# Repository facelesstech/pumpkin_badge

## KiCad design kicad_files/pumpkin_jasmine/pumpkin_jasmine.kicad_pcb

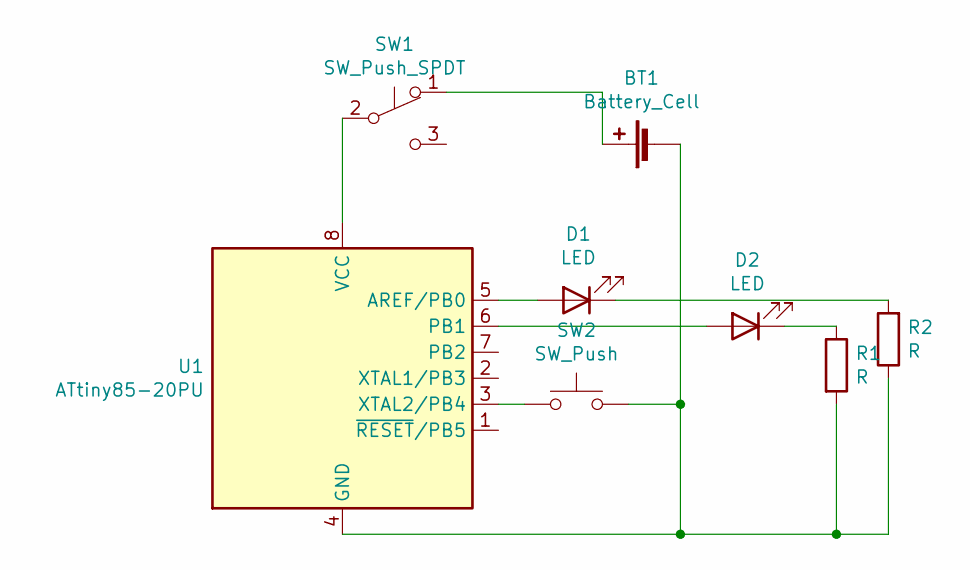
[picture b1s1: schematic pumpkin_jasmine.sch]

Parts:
BT1: Battery_Cell; Keystone_3034_1x20mm-CoinCell
D1, D2: LED; LED_D3.0mm
R1, R2: R; R_Axial_DIN0414_L11.9mm_D4.5mm_P7.62mm_Vertical
SW1: SW_Push_SPDT; 3_pin_switch_smd_side_mount
SW2: SW_Push; SMD_2pin_button_custom
U1: ATtiny85-20PU; DIP-8_W7.62mm

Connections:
unnamed: BT1.1 (+), SW1.1 (A)
unnamed: BT1.2 (-), R1.2, R2.1, SW2.2, U1.4 (GND)
unnamed: D1.1 (K), R2.2
unnamed: D1.2 (A), U1.5 (AREF/PB0)
unnamed: D2.1 (K), R1.1
unnamed: D2.2 (A), U1.6 (PB1)
unnamed: SW1.2 (B), U1.8 (VCC)
unnamed: SW2.1, U1.3 (XTAL2/PB4)

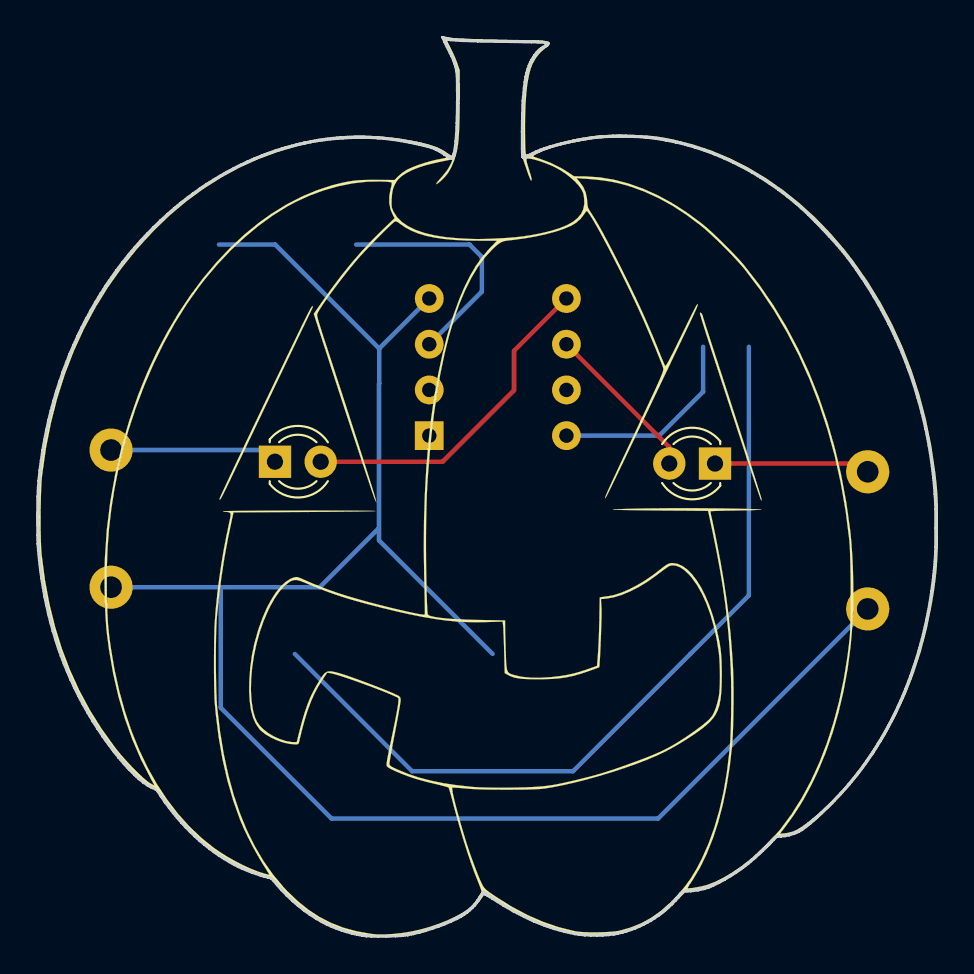
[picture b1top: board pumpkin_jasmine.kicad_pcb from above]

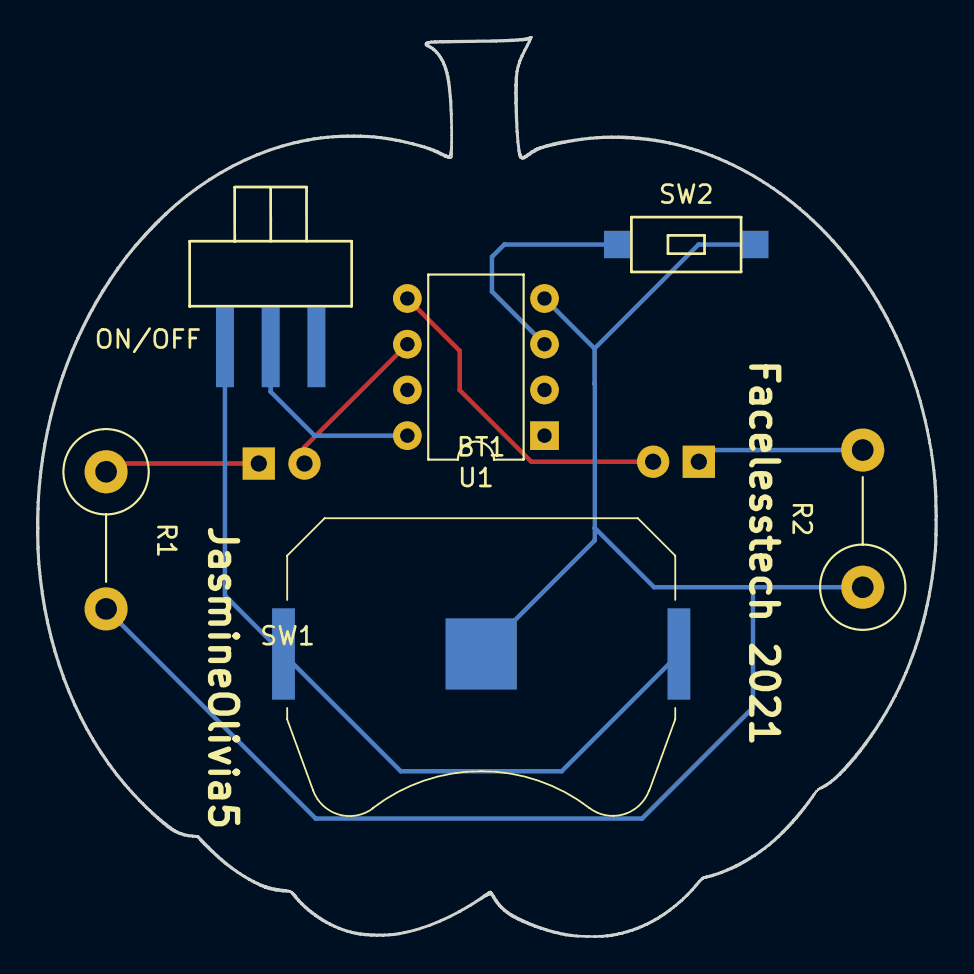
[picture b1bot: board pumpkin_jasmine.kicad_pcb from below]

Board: 2 copper layers, 50.0 x 50.0 mm, 9 parts (6 on the bottom side), 8 nets.

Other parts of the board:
Ref**: Val**; new_pump

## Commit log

2021-10-17 arduino code for pumpkin badge
2021-10-17 kicad files
